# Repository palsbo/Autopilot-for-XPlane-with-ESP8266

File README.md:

# Autopilot
An ESP8266 based Autopilot for X-Plane
This is a hardware based autopilot to be useed together with X-Plane (tested on X-Plane v10.50).

Hardware:
The printed circuit is developed in Target3001
OBS! read the file 'corrections.txt' before mounting the printed curcuit.

Software:
The software for the ESP8266 is in the Arduino folder together with all required libraries.
(for Arduino IDE)

Project details here: http://palsbo.com/xplane/Autopilot.html 

Files in this GitHup are the newest

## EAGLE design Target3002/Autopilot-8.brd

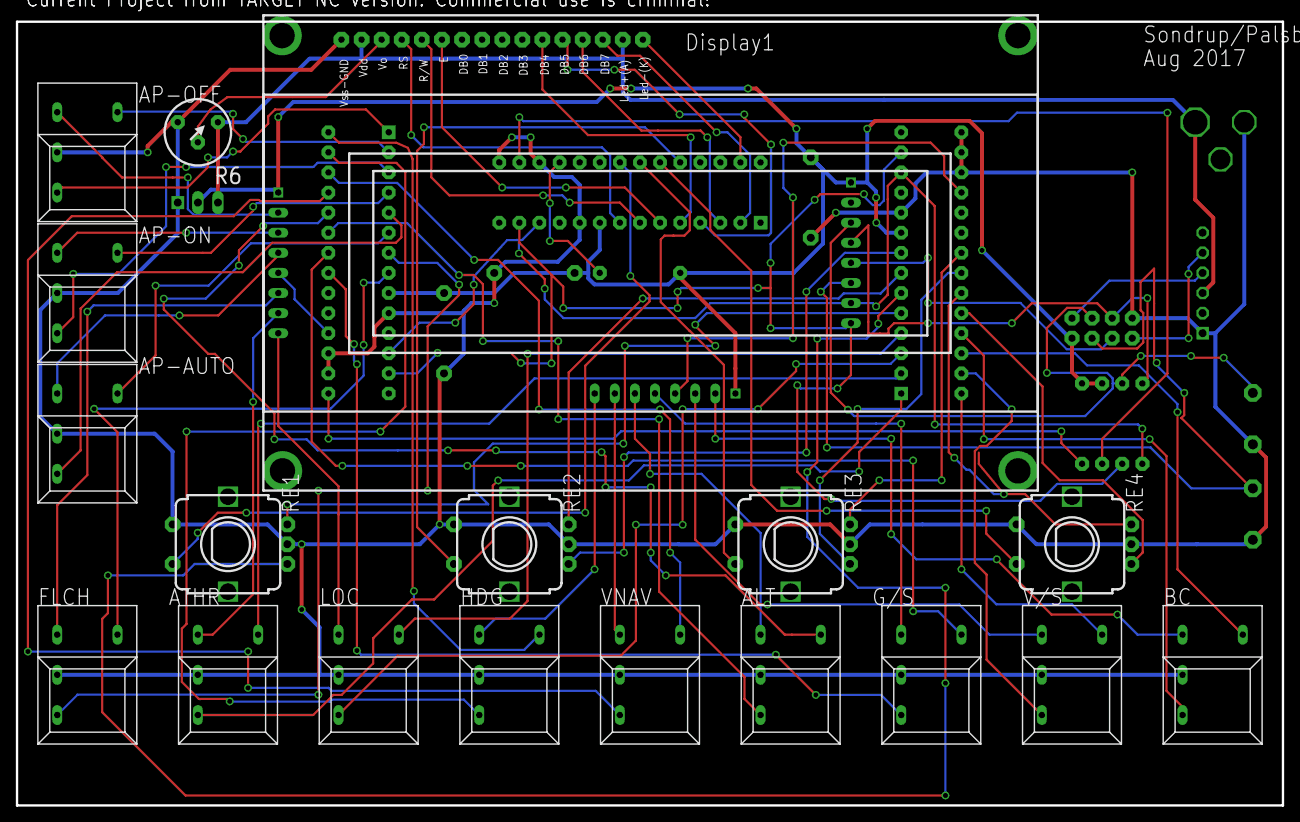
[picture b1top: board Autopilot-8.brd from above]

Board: 2 copper layers, 160.0 x 99.1 mm, 38 parts (0 on the bottom side), 73 nets.

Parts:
C1: 100nF; 4X13R10,16_11
C2: 100nF; 4X13R10,16_12
C3: 100nF; 4X13R10,16_15
Display1: LCD_2004; LCD2004_13
IC2: ESP8266_ESP01; ESP01_6
J1: Einlöt-DC-Buchse_2.5; EINLÖT-DC-BUCHSE_2.5MM_36
J3: PinHeader_1x06_W_2,54; 1X06-90_32
PE1: PORTEXPANDER MCP23017; PortExpander_Gehäuse:PDIP-28_4
PE2: PORTEXPANDER MCP23017; PortExpander_Gehäuse:PDIP-28_5
PE3: PORTEXPANDER MCP23017; PortExpander_Gehäuse:PDIP-28_14
R1: 330; 0207_7
R2: 330; 0207_8
R3: 3,3K; 0207_17
R4: 3,3K; 0207_18
R5: 3,3K; 0207_19
R6: 10K; POTI_PD84_35
R10: 8PIN-NW; SIL8_16
R11: 8PIN-NW; SIL8_9
R12: 8PIN-NW; SIL8_10
RE1: IAS; STEC12E08_3
RE2: HDG; STEC12E08_2
RE3: ALT; STEC12E08_1
RE4: V/S; STEC12E08_0
S1: PHAP3362A; KURZHUBTASTER_DURCHSTECKMONT._33
S2: PHAP3362A; KURZHUBTASTER_DURCHSTECKMONT._34
SD1: TASTER_DIGITAST_STD-LED-SJS; TASTER_DIGITAST_STD(#1)(#1)_20
SD2: TASTER_DIGITAST_STD-LED-SJS; TASTER_DIGITAST_STD(#1)(#1)_21
SD3: TASTER_DIGITAST_STD-LED-SJS; TASTER_DIGITAST_STD(#1)(#1)_22
SD4: TASTER_DIGITAST_STD-LED-SJS; TASTER_DIGITAST_STD(#1)(#1)_23
SD5: TASTER_DIGITAST_STD-LED-SJS; TASTER_DIGITAST_STD(#1)(#1)_24
SD6: TASTER_DIGITAST_STD-LED-SJS; TASTER_DIGITAST_STD(#1)(#1)_25
SD7: TASTER_DIGITAST_STD-LED-SJS; TASTER_DIGITAST_STD(#1)(#1)_26
SD8: TASTER_DIGITAST_STD-LED-SJS; TASTER_DIGITAST_STD(#1)(#1)_27
SD9: TASTER_DIGITAST_STD-LED-SJS; TASTER_DIGITAST_STD(#1)(#1)_28
SD10: TASTER_DIGITAST_STD-LED-SJS; TASTER_DIGITAST_STD(#1)(#1)_29
SD11: TASTER_DIGITAST_STD-LED-SJS; TASTER_DIGITAST_STD(#1)(#1)_30
SD12: TASTER_DIGITAST_STD-LED-SJS; TASTER_DIGITAST_STD(#1)(#1)_31
X1: LM1085IT-3.3; TO220_37

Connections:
5V: Display1.2, Display1.15, J1.1, J3.3, R6.1, X1.3
ALT: PE2.23, SD9.3
AP-AUTO: PE2.5, SD3.3
AP-OFF: PE2.1, SD1.3
AP-ON: PE2.3, SD2.3
APE2.0: PE2.15, R5.1
ATHR: PE1.1, SD5.3
B: PE1.23, RE4.3
BC: PE1.25, SD12.3
D4: Display1.11, PE3.5
D6: Display1.13, PE3.3
ESP-RST: IC2.2, R10.6, S2.2
FLCH: PE2.7, SD4.3
GND: C1.1, C2.1, C3.2, Display1.1, IC2.8, J1.3, J3.1, PE1.10, PE1.15, PE1.16, PE1.17, PE2.10, PE2.16, PE2.17, PE3.10, PE3.15, PE3.17, R6.3, RE1.2, RE1.4, RE2.2, RE2.4, RE3.2, RE3.4, RE4.2, RE4.4, S1.2, S2.1, SD1.2, SD2.2, SD3.2, SD4.2, SD5.2, SD6.2, SD7.2, SD8.2, SD9.2, SD10.2, SD11.2, SD12.2, X1.1
GPIO0/Prog: IC2.6, R2.2, R10.3, S1.1
GPIO2: IC2.7, R1.2, R10.4
GS: PE2.21, SD10.3
HDG: PE2.27, SD7.3
LED-ALT: PE2.24, SD9.4
LED-AP-AUTP: PE2.6, SD3.4
LED-AP-OFF: PE2.2, SD1.4
LED-AP-ON: PE2.4, SD2.4
LED-ATHR: PE1.2, SD5.4
LED-BC: PE1.26, SD12.4
LED-FLCH: PE2.8, SD4.4
LED-GS: PE2.22, SD10.4
LED-HDG: PE2.28, SD7.4
LED-LOC: PE1.4, SD6.4
LED-VNAV: PE2.26, SD8.4
LED-VS: PE1.28, SD11.4
LOC: PE1.3, SD6.3
PE2A1: PE1.22, RE3.1
PE2B4: PE1.5, RE1.3
PE2B5: Display1.12, PE3.4
PE2B6: PE1.7, RE2.3
R/W: Display1.5, PE3.7
RESET: PE1.18, R12.4
RS: Display1.4, PE3.8
SCL: PE1.12, PE2.12, PE3.12, R1.1, R10.7
SDA: PE1.13, PE2.13, PE3.13, R2.1, R10.8
Sig$24: PE1.21, RE3.3
Sig$27: PE1.8, RE2.1
Sig$29: PE1.6, RE1.1
Sig$107: R12.2, SD12.5
Sig$108: R12.7, SD8.5
Sig$118: IC2.3, R10.5
Sig$129: R12.3, SD11.5
Sig$131: R12.6, SD9.5
Sig$132: R12.8, SD7.5
Sig$137: R11.2, SD1.5
Sig$138: R11.3, SD2.5
Sig$139: R11.4, SD3.5
Sig$140: PE2.18, R11.5
Sig$141: R11.6, SD4.5
Sig$142: R11.7, SD5.5
Sig$143: R11.8, SD6.5
Sig$195: Display1.14, PE3.2
Sig$208: Display1.6, PE3.6
Sig$209: PE3.18, R3.1
Sig$211: PE3.16, R4.1
Sig$230: R12.5, SD10.5
Sig$260: Display1.16, PE3.27
Sig$269: IC2.5, J3.4
TxD: IC2.4, J3.5
VCC3.3: C1.2, C2.2, C3.1, IC2.1, PE1.9, PE2.9, PE3.9, R3.2, R4.2, R5.2, R10.1, R11.1, R12.1, X1.2
VNAV: PE2.25, SD8.3
VS: PE1.27, SD11.3
Vo: Display1.3, R6.2
ss0: PE3.21, RE1.5
ss1: PE3.22, RE3.5
ss2: PE3.23, RE4.5
ss3: PE3.24, RE2.5
xx: PE1.24, RE4.1

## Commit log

2016-10-07 Autopilot for X-Plane based on ESP8266
2016-10-07 modified: README.md deleted: Target3002/Autopilot-8.T3001 deleted: Target3002/Autopilot-8.brd deleted: Target3002/Autopilot-8.sch deleted: Target3002/XGerber/Autopilot-8.Apr deleted: Target3002/XGerb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
2016-10-07 First Upload
2016-10-07 Readme changed
2016-10-07 Included Link
2016-10-07 Canges
2016-10-08 Version 1.1
2017-07-03 new version 4.9
2017-07-03 renew
